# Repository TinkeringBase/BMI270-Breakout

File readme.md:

[한국어](https://github.com/TinkeringBase/BMI270-Breakout/blob/main/readme-ko.md)
# TinkeringBase BMI270 IMU breakout
\
Sensor breakout using Bosch Sensortec's BMI270 6DoF IMU, supports Sparkfun Qwiic system. 

## Specification
Supply Voltage (VDD): 1.71~3.6V \
Logic Low (VIL): 0.3\*VDD max \
Logic High (VIH): 0.7\*VDD min \
Current consumption: around 1mA at performance mode \
for more information, see [BMI270 techdata](https://www.bosch-sensortec.com/products/motion-sensors/imus/bmi270/#technical)

## I2C address
the module uses I2C address 0b1101000 (0x68) by default. to change it to 0b1101001 (0x69), solder the jumper at the back side of the module.

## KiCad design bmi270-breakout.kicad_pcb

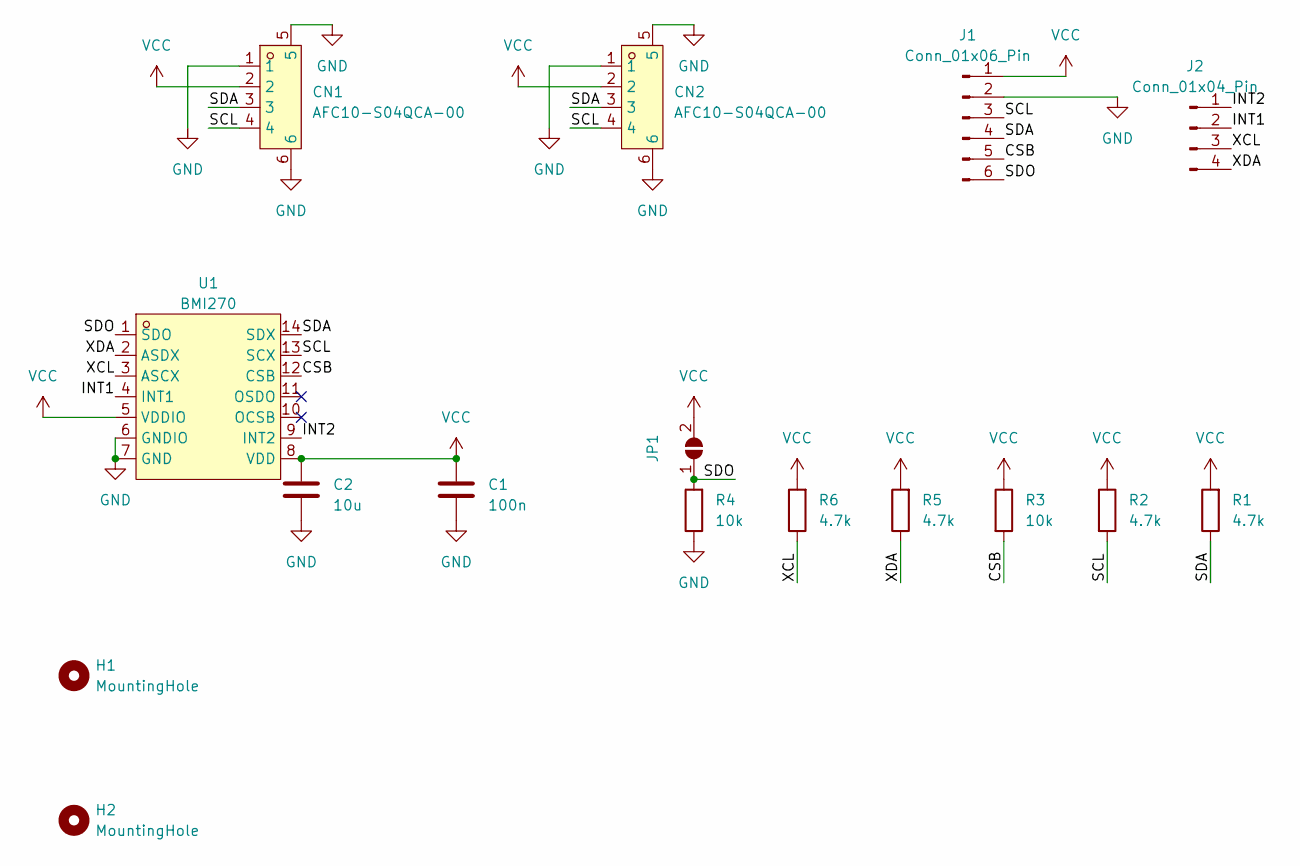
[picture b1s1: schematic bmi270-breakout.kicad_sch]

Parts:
C1: 100n; C_0402_1005Metric
C2: 10u; C_0603_1608Metric
CN1, CN2: AFC10-S04QCA-00; CONN-SMD_AFC10-S04QCA-00; LCSC Part C2764183
H1, H2: MountingHole; MountingHole_2.2mm_M2
J1: Conn_01x06_Pin; PinHeader_1x06_P2.54mm_Vertical
J2: Conn_01x04_Pin; PinHeader_1x04_P2.54mm_Vertical
JP1: SolderJumper_2_Open; SolderJumper-2_P1.3mm_Open_TrianglePad1.0x1.5mm
R1, R2, R5, R6: 4.7k; R_0402_1005Metric
R3, R4: 10k; R_0402_1005Metric
U1: BMI270; LGA-14_L3.0-W2.5-P0.50-BR; LCSC Part C2836813

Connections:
/CSB: J1.5, R3.2, U1.12 (CSB)
/INT1: J2.2, U1.4 (INT1)
/INT2: J2.1, U1.9 (INT2)
/SCL: CN1.4, CN2.4, J1.3, R2.2, U1.13 (SCX)
/SDA: CN1.3, CN2.3, J1.4, R1.1, U1.14 (SDX)
/SDO: J1.6, JP1.1 (A), R4.2, U1.1 (SDO)
/XCL: J2.3, R6.1, U1.3 (ASCX)
/XDA: J2.4, R5.1, U1.2 (ASDX)
GND: C1.2, C2.2, CN1.1, CN1.5, CN1.6, CN2.1, CN2.5, CN2.6, J1.2, R4.1, U1.6 (GNDIO), U1.7 (GND)
VCC: C1.1, C2.1, CN1.2, CN2.2, J1.1, JP1.2 (B), R1.2, R2.1, R3.1, R5.2, R6.2, U1.5 (VDDIO), U1.8 (VDD)

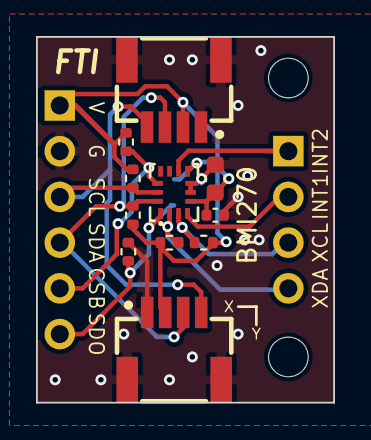
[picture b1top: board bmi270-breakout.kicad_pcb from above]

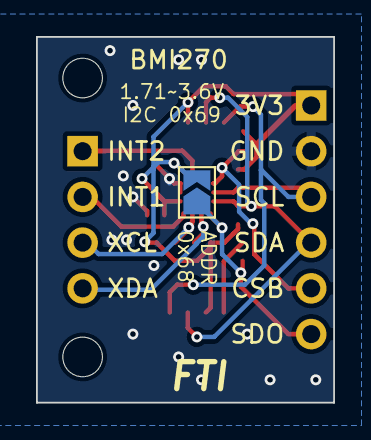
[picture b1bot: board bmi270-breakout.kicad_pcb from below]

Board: 2 copper layers, 16.5 x 20.3 mm, 16 parts (3 on the bottom side), 10 nets.

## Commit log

2024-01-02 add dimensions mark, preview image files
2024-01-02 clean up, correct mistakes
2024-01-03 forgot pad labels
2024-02-04 OOPS
2024-02-19 update license
2024-02-28 documentation, migrate to kicad 8, fix address jumper, add branding
2024-02-28 schematics
2024-03-04 fix readme
2024-04-16 fix qwiic pinout, rework footprint
2024-04-16 allign mounting holes
2024-05-10 gitignore and pcb
2024-09-19 redo silkscreen
2024-12-11 redo layout
2024-12-11 use higher pullup, refine schematic
2024-12-11 silkscreen
